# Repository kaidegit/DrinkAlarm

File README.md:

# 提醒喝水器

本项目致力于复刻[何同学视频](https://www.bilibili.com/video/BV1244y1p7kt)中的智能杯垫，并添加更多的功能。~~才不是因为何同学做的开灯方案太没意义呢~~

## 方案设计

* 主芯片使用乐鑫ESP32，能在提供足够的性能的同时提供一个够用的互联网连接

* 检测杯子存在采用光电传感器，价格低廉，识别准确，美中不足需要在外壳上开孔

* 提醒方案采用[Server酱](https://sct.ftqq.com/)的微信推送，同时板载蜂鸣器，可自行修改代码使用

* 外壳采用PETG打印而成，可自行选择其他材料以适应盛放开水的杯子

## PCB设计

PCB使用Altium Designer和KiCAD设计。由于前后距离略长，PCB分为两块，一块为Type-C小板，一块为主PCB，两者通过杜邦线相连。推荐使用XH2.54系列端子以避免潜在的接触不良。推荐使用长度10或15厘米的线材。

## 外壳设计

外壳使用SoildWorks设计（大版本2020）。设计了上盖和底壳，两者通过长螺丝连接。长螺丝推荐使用M3 45mm，其他螺丝推荐使用M3 5mm。对于外壳的修改意见，欢迎提交issue和PR。

## 程序设计

程序基于ESP-IDF框架，并使用Arduino as a ESP-IDF component。预计后期将移除。

程序主要功能为设定报警时间，获取联网信息，获取在线时间并显示，计时杯子存在时间并推送等。

主要流程如下：

## 效果图

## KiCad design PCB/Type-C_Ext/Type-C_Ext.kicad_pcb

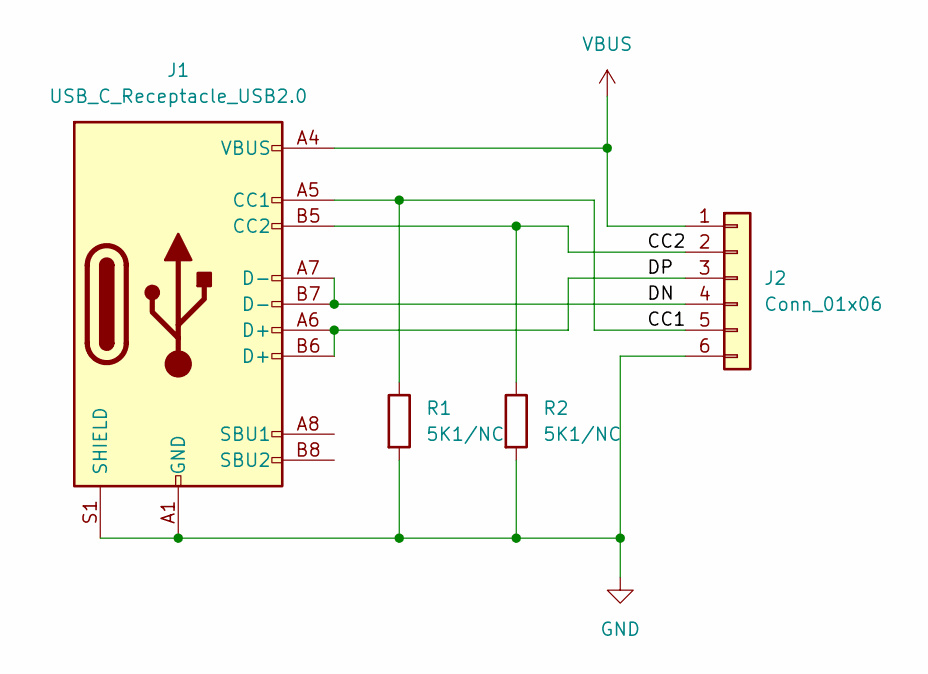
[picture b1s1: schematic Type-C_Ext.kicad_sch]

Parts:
J1: USB_C_Receptacle_USB2.0; USB_C_Receptacle_HRO_TYPE-C-31-M-12
J2: Conn_01x06; PinSocket_1x06_P2.54mm_Horizontal
R1, R2: 5K1/NC; R_0603_1608Metric_Pad0.98x0.95mm_HandSolder

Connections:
/CC1: J1.A5 (CC1), J2.5, R1.1
/CC2: J1.B5 (CC2), J2.2, R2.1
/DN: J1.A7 (D-), J1.B7 (D-), J2.4
/DP: J1.A6 (D+), J1.B6 (D+), J2.3
GND: J1.A1 (GND), J1.A12 (GND), J1.B1 (GND), J1.B12 (GND), J1.S1 (SHIELD), J2.6, R1.2, R2.2
VBUS: J1.A4 (VBUS), J1.A9 (VBUS), J1.B4 (VBUS), J1.B9 (VBUS), J2.1

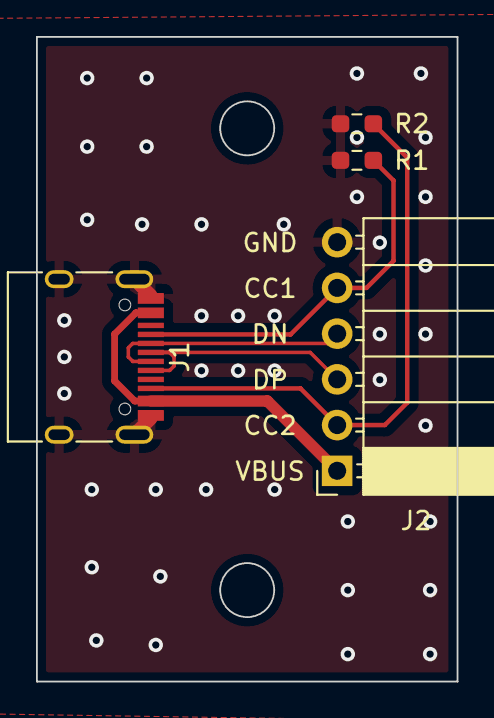
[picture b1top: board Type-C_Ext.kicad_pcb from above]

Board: 2 copper layers, 23.4 x 35.8 mm, 4 parts (0 on the bottom side), 6 nets.

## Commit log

2022-02-11 init pio
2022-02-12 init idf prj
2022-02-12 init arduino in idf
2022-02-12 test blink
2022-02-14 add u8g2 lib
2022-02-14 update submodule's url
2022-02-15 add setting logic
2022-02-17 add wifi info read and write
2022-02-17 add alarm setting read and write logic
2022-02-18 add lvgl
2022-02-18 use u8g2 to replace lvgl
2022-02-18 fix cmake of u8g2
2022-02-18 写完了大部分的逻辑
2022-02-18 差不多完工啦
2022-02-22 添加到达定时时间发送http.get的功能
2022-02-24 add 3d models & pcbs
2022-02-24 add license
2022-03-02 remove arduino component dependency
